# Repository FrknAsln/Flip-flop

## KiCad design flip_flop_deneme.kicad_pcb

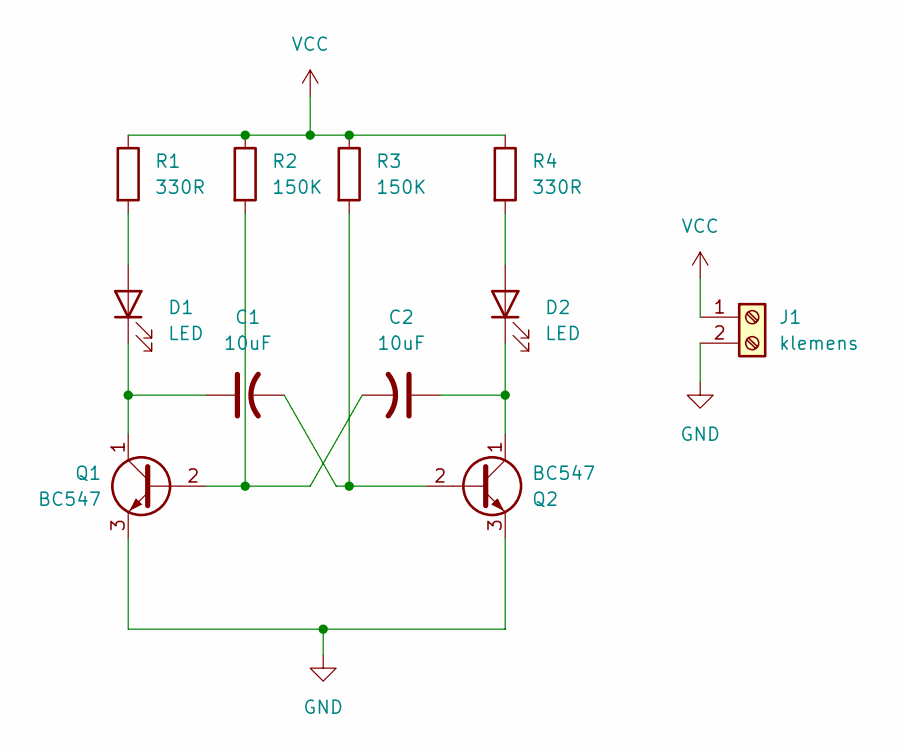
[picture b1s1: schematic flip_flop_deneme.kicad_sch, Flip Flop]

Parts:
C1, C2: 10uF; C_Radial_D4.0mm_H5.0mm_P1.50mm
D1, D2: LED; LED_D3.0mm
J1: klemens; TerminalBlock_MaiXu_MX126-5.0-02P_1x02_P5.00mm
Q1, Q2: BC547; TO-92_Inline
R1, R4: 330R; R_Axial_DIN0207_L6.3mm_D2.5mm_P10.16mm_Horizontal
R2, R3: 150K; R_Axial_DIN0207_L6.3mm_D2.5mm_P10.16mm_Horizontal

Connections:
GND: J1.2, Q1.3 (E), Q2.3 (E)
unnamed: D1.2 (A), R1.2
unnamed: C1.1, D1.1 (K), Q1.1 (C)
unnamed: D2.2 (A), R4.2
unnamed: C2.1, D2.1 (K), Q2.1 (C)
unnamed: C2.2, Q1.2 (B), R2.2
unnamed: C1.2, Q2.2 (B), R3.2
VCC: J1.1, R1.1, R2.1, R3.1, R4.1

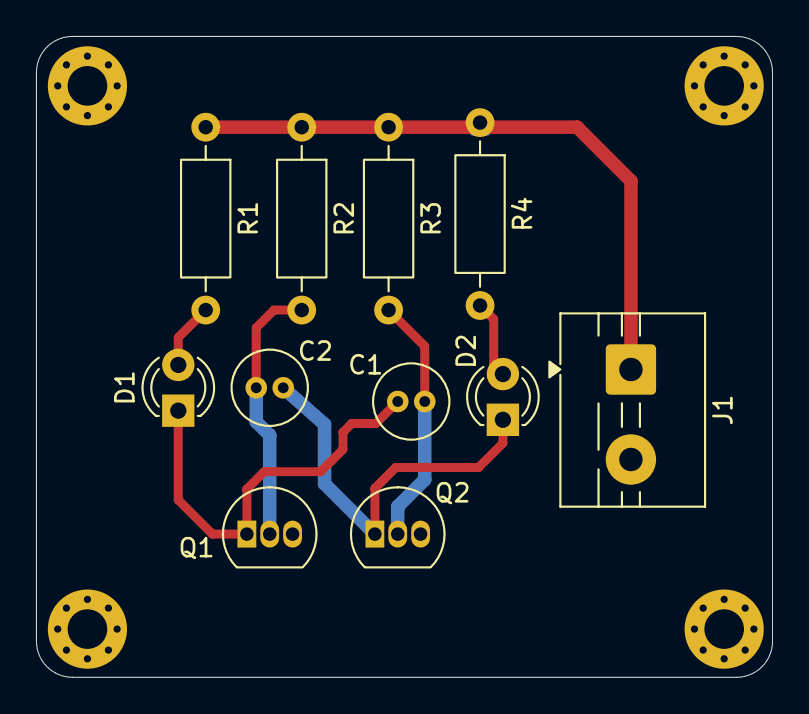
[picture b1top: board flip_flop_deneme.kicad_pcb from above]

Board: 2 copper layers, 40.9 x 35.6 mm, 11 parts (0 on the bottom side), 8 nets.
